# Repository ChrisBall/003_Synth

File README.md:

# 003_Synth
Code &amp; files for making my audio-lib based synth; 003

Based on a teensy 4.0 with assoc. audio board.

The synth is actually 2 devices - a teensy 4.0 with audio board and a separate "nano every"-based midi controller, with 48 pots, a rotary encoder and OLED display. 

Description of the contents of the code folder:

-"003_synth_main" contains the main arduino sketch.

-"Processing_003_controller_board" contains a basic processing sketch for controlling the synth using [the midibus](https://github.com/sparks/themidibus) library.

-"ctrlr interface" contains a similar midi interface for the [ctrlr software](https://github.com/RomanKubiak/ctrlr).

-"modified audio lib files" contains a modified delay effect for tape simulation. You'll need to replace the originals in the teensy audio lib folder.

-"nano_controller" contains the code that runs on the HMI controller.

You can use this code without building a controller - the synth can be controlled via MIDI. There is a processing program or ctrlr interface in the code folder to facilitate this.

Compilation notes:

-To compile my digital "tape" delay module you'll need to replace the teensy audio lib files (effect_delay.cpp and effect_delay.h) with my versions in the "modified audio lib files" folder.
-Build with "smallest code" option

To get it making a sound, there's some extra work:

-You'll need to set the master volume (CC44, channel 3 - the device only responds to controller values on channel 3). 
-To get sound through the effects chain, set the two distortion gains (CC25, CC41 - channel 3) which default to 0.
-To save a preset (SD card required) send program change on channel 16. To load: program change on channel 3. Presets are saved as plain text in folder "/PRESETS/" on the SD.

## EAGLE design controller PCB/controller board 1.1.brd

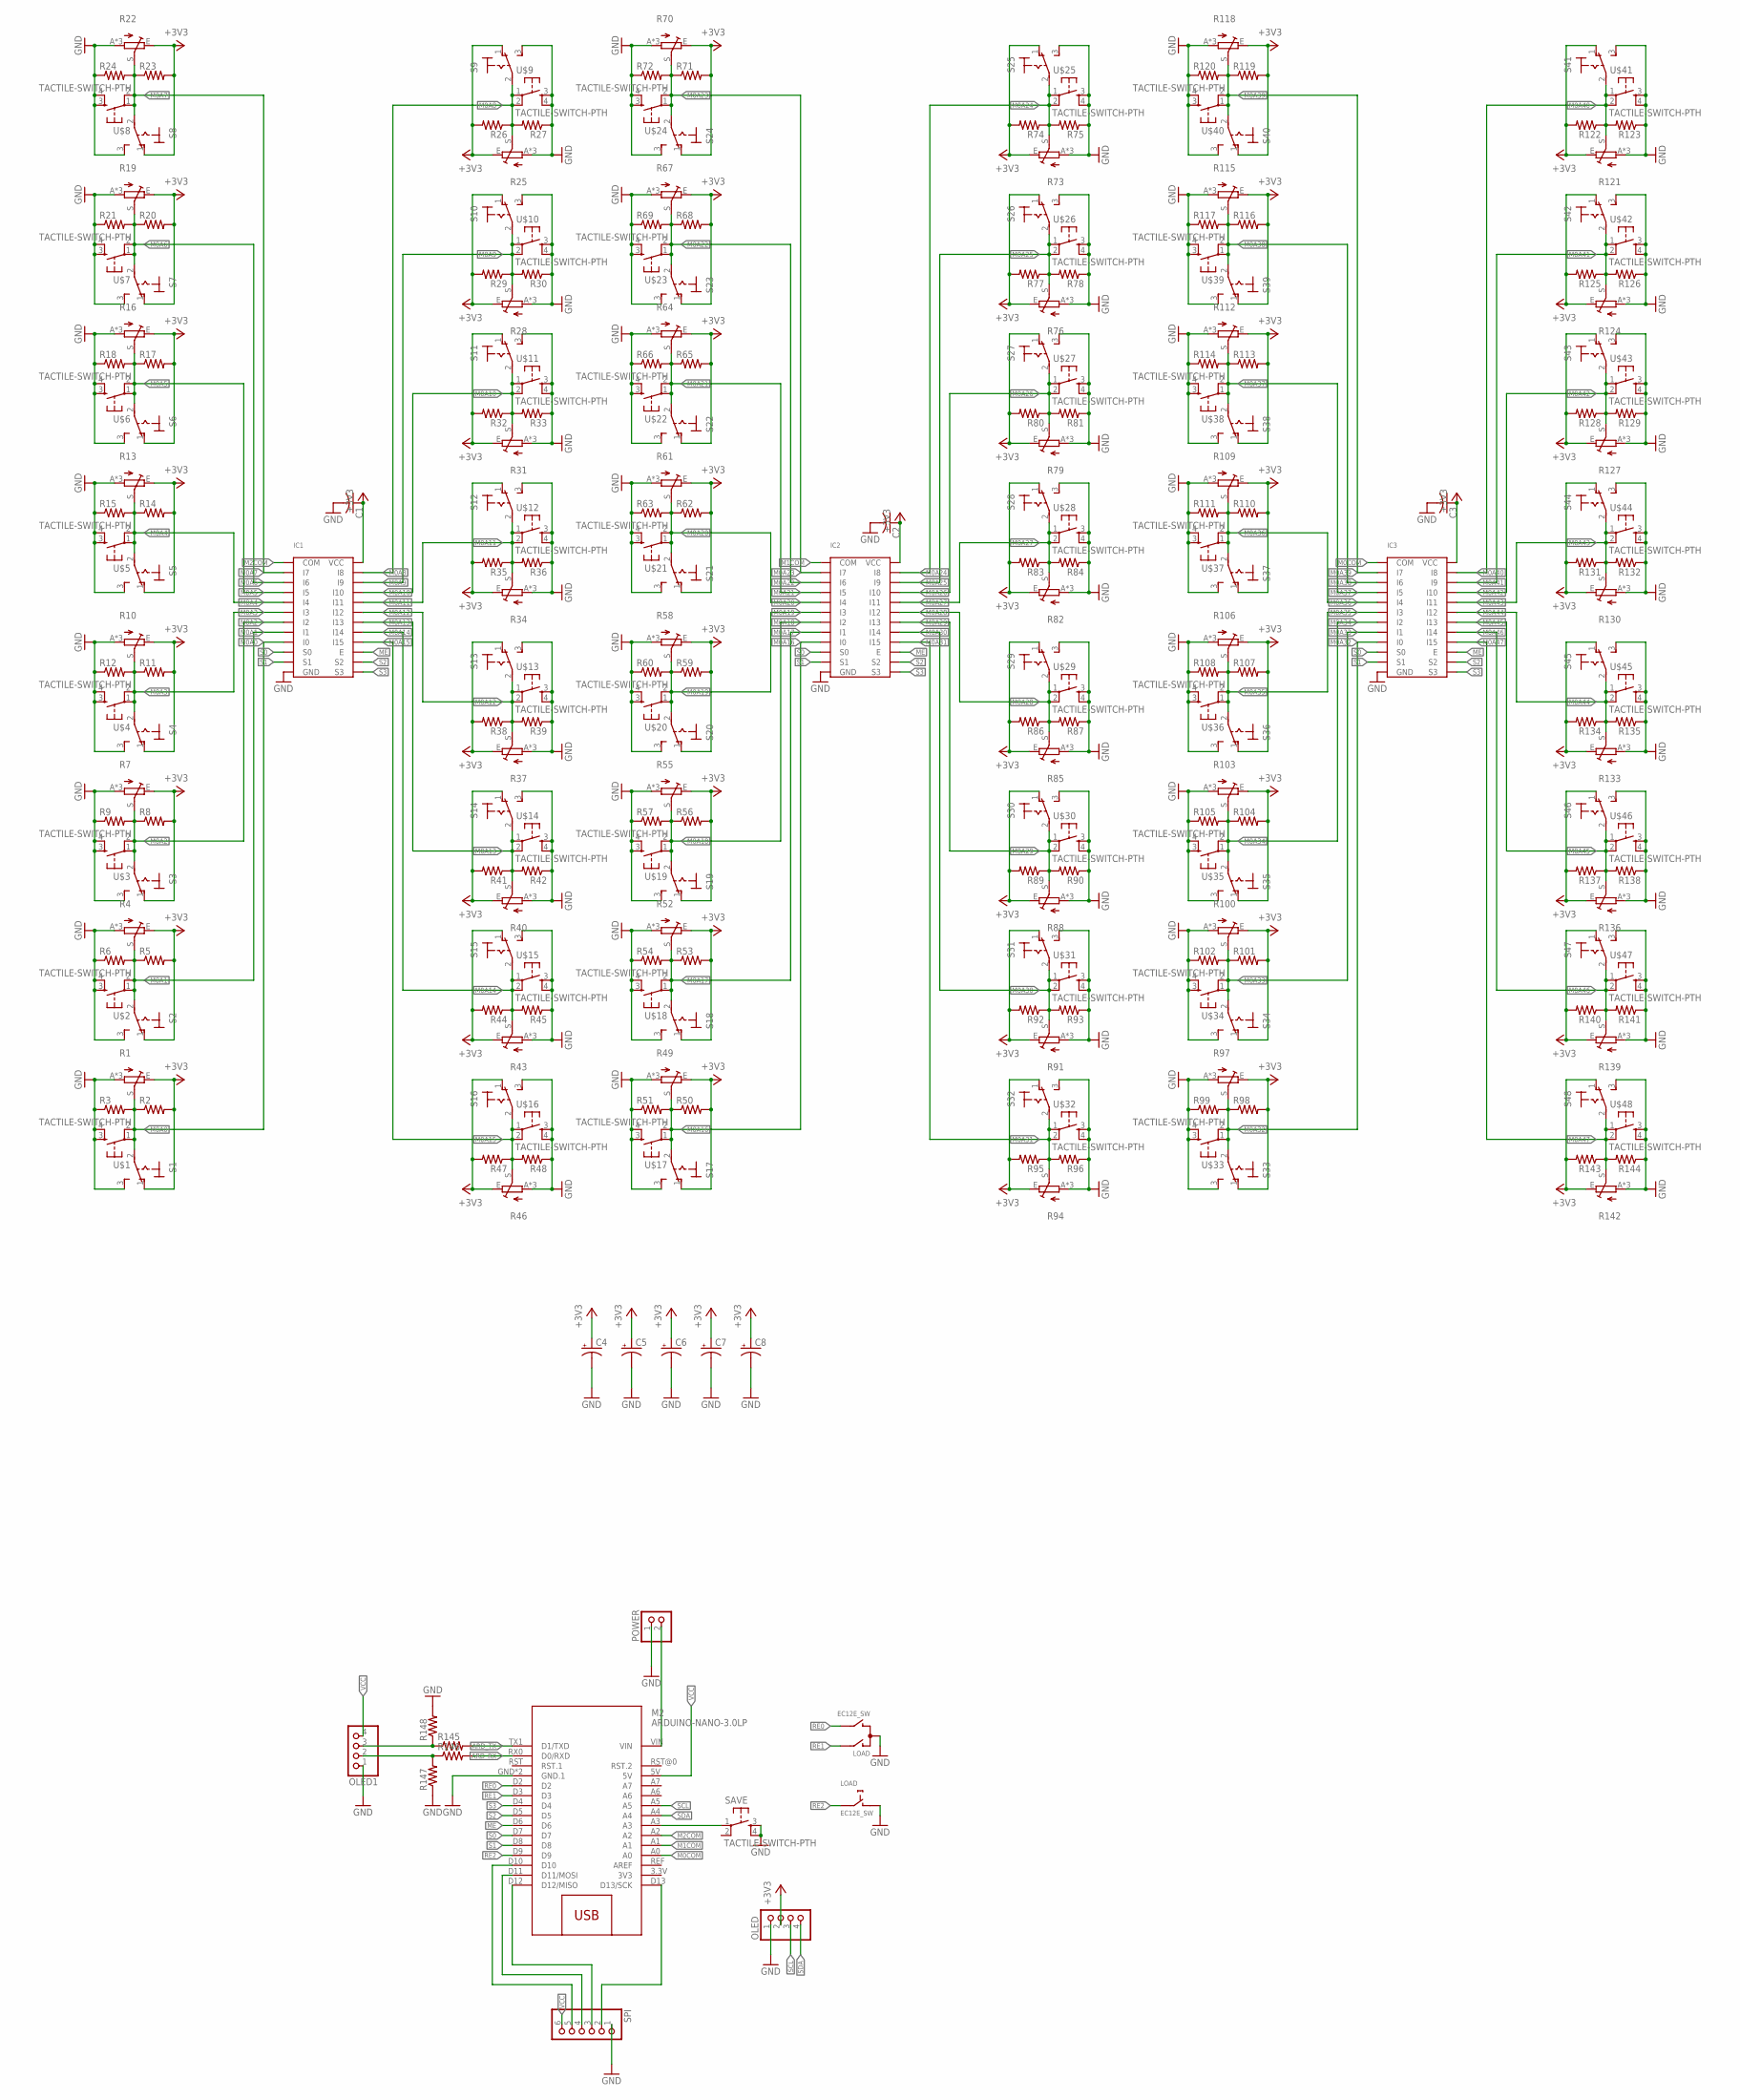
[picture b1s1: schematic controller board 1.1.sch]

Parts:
C1, C2, C3: C-USC0805; C0805
C4, C5, C6, C7, C8: CPOL-USE2.5-6; E2,5-6
IC1, IC2, IC3: CD74HC4067SM96; LP24SSOP
LOAD: EC12E_SW; ALPS_EC12E_SW
M2: ARDUINO-NANO-3.0LP; ARDUINO-NANO-3.0_LONGPADS
OLED, OLED1: PINHD-1X4; 1X04
POWER: PINHD-1X2; 1X02
R1, R4, R7, R10, R13, R16, R19, R22, R25, R28, R31, R34, R37, R40, R43, R46, R49, R52, R55, R58, R61, R64, R67, R70, R73, R76, R79, R82, R85, R88, R91, R94, R97, R100, R103, R106, R109, R112, R115, R118, R121, R124, R127, R130, R133, R136, R139, R142: TDS3_TRIM_EU-RK09LS; TDS3_RK09L
R2, R3, R5, R6, R8, R9, R11, R12, R14, R15, R17, R18, R20, R21, R23, R24, R26, R27, R29, R30, R32, R33, R35, R36, R38, R39, R41, R42, R44, R45, R47, R48, R50, R51, R53, R54, R56, R57, R59, R60, R62, R63, R65, R66, R68, R69, R71, R72, R74, R75, R77, R78, R80, R81, R83, R84, R86, R87, R89, R90, R92, R93, R95, R96, R98, R99, R101, R102, R104, R105, R107, R108, R110, R111, R113, R114, R116, R117, R119, R120, R122, R123, R125, R126, R128, R129, R131, R132, R134, R135, R137, R138, R140, R141, R143, R144, R145, R146, R147, R148: R-US_M0805; M0805
S1, S2, S3, S4, S5, S6, S7, S8, S9, S10, S11, S12, S13, S14, S15, S16, S17, S18, S19, S20, S21, S22, S23, S24, S25, S26, S27, S28, S29, S30, S31, S32, S33, S34, S35, S36, S37, S38, S39, S40, S41, S42, S43, S44, S45, S46, S47, S48: M9040P
SAVE: TACTILE-SWITCH-PTH; TAC-SWITCH-PTH
SPI: PINHD-1X6; 1X06
U$1, U$2, U$3, U$4, U$5, U$6, U$7, U$8, U$9, U$10, U$11, U$12, U$13, U$14, U$15, U$16, U$17, U$18, U$19, U$20, U$21, U$22, U$23, U$24, U$25, U$26, U$27, U$28, U$29, U$30, U$31, U$32, U$33, U$34, U$35, U$36, U$37, U$38, U$39, U$40, U$41, U$42, U$43, U$44, U$45, U$46, U$47, U$48: TACTILE-SWITCH-PTH; TAC-SWITCH-PTH

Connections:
3V3: M2.3.3V (3V3)
ARD_RX: M2.RX0 (D0/RXD), R146.2
ARD_TX: M2.TX1 (D1/TXD), R145.2
GND: C1.2, C2.2, C3.2, C4.-, C5.-, C6.-, C7.-, C8.-, IC1.GND, IC2.GND, IC3.GND, LOAD.C, LOAD.D (1), M2.GND (GND.1), M2.GND@1 (GND.1), OLED.1, OLED1.1, POWER.1, R1.A, R1.SNAPL (A), R1.SNAPR (A), R3.1, R4.A, R4.SNAPL (A), R4.SNAPR (A), R6.1, R7.A, R7.SNAPL (A), R7.SNAPR (A), R9.1, R10.A, R10.SNAPL (A), R10.SNAPR (A), R12.1, R13.A, R13.SNAPL (A), R13.SNAPR (A), R15.1, R16.A, R16.SNAPL (A), R16.SNAPR (A), R18.1, R19.A, R19.SNAPL (A), R19.SNAPR (A), R21.1, R22.A, R22.SNAPL (A), R22.SNAPR (A), R24.1, R25.A, R25.SNAPL (A), R25.SNAPR (A), R27.1, R28.A, R28.SNAPL (A), R28.SNAPR (A), R30.1, R31.A, R31.SNAPL (A), R31.SNAPR (A), R33.1, R34.A, R34.SNAPL (A), R34.SNAPR (A), R36.1, R37.A, R37.SNAPL (A), R37.SNAPR (A), R39.1, R40.A, R40.SNAPL (A), R40.SNAPR (A), R42.1, R43.A, R43.SNAPL (A), R43.SNAPR (A), R45.1, R46.A, R46.SNAPL (A), R46.SNAPR (A), R48.1, R49.A, R49.SNAPL (A), R49.SNAPR (A), R51.1, R52.A, R52.SNAPL (A), R52.SNAPR (A), R54.1, R55.A, R55.SNAPL (A), R55.SNAPR (A), R57.1, R58.A, R58.SNAPL (A), R58.SNAPR (A), R60.1, R61.A, R61.SNAPL (A), R61.SNAPR (A), R63.1, R64.A, R64.SNAPL (A), R64.SNAPR (A), R66.1, R67.A, R67.SNAPL (A), R67.SNAPR (A), R69.1, R70.A, R70.SNAPL (A), R70.SNAPR (A), R72.1, R73.A, R73.SNAPL (A), R73.SNAPR (A), R75.1, R76.A, R76.SNAPL (A), R76.SNAPR (A), R78.1, R79.A, R79.SNAPL (A), R79.SNAPR (A), R81.1, R82.A, R82.SNAPL (A), R82.SNAPR (A), R84.1, R85.A, R85.SNAPL (A), R85.SNAPR (A), R87.1, R88.A, R88.SNAPL (A), R88.SNAPR (A), R90.1, R91.A, R91.SNAPL (A), R91.SNAPR (A), R93.1, R94.A, R94.SNAPL (A), R94.SNAPR (A), R96.1, R97.A, R97.SNAPL (A), R97.SNAPR (A), R99.1, R100.A, R100.SNAPL (A), R100.SNAPR (A), R102.1, R103.A, R103.SNAPL (A), R103.SNAPR (A), R105.1, R106.A, R106.SNAPL (A), R106.SNAPR (A), R108.1, R109.A, R109.SNAPL (A), R109.SNAPR (A), R111.1, R112.A, R112.SNAPL (A), R112.SNAPR (A), R114.1, R115.A, R115.SNAPL (A), R115.SNAPR (A), R117.1, R118.A, R118.SNAPL (A), R118.SNAPR (A), R120.1, R121.A, R121.SNAPL (A), R121.SNAPR (A), R123.1, R124.A, R124.SNAPL (A), R124.SNAPR (A), R126.1, R127.A, R127.SNAPL (A), R127.SNAPR (A), R129.1, R130.A, R130.SNAPL (A), R130.SNAPR (A), R132.1, R133.A, R133.SNAPL (A), R133.SNAPR (A), R135.1, R136.A, R136.SNAPL (A), R136.SNAPR (A), R138.1, R139.A, R139.SNAPL (A), R139.SNAPR (A), R141.1, R142.A, R142.SNAPL (A), R142.SNAPR (A), R144.1, R147.1, R148.2, S1.3 (S), S2.3 (S), S3.3 (S), S4.3 (S), S5.3 (S), S6.3 (S), S7.3 (S), S8.3 (S), S9.3 (S), S10.3 (S), S11.3 (S), S12.3 (S), S13.3 (S), S14.3 (S), S15.3 (S), S16.3 (S), S17.3 (S), S18.3 (S), S19.3 (S), S20.3 (S), S21.3 (S), S22.3 (S), S23.3 (S), S24.3 (S), S25.3 (S), S26.3 (S), S27.3 (S), S28.3 (S), S29.3 (S), S30.3 (S), S31.3 (S), S32.3 (S), S33.3 (S), S34.3 (S), S35.3 (S), S36.3 (S), S37.3 (S), S38.3 (S), S39.3 (S), S40.3 (S), S41.3 (S), S42.3 (S), S43.3 (S), S44.3 (S), S45.3 (S), S46.3 (S), S47.3 (S), S48.3 (S), SAVE.3, SAVE.4, SPI.1, U$1.3, U$1.4, U$2.3, U$2.4, U$3.3, U$3.4, U$4.3, U$4.4, U$5.3, U$5.4, U$6.3, U$6.4, U$7.3, U$7.4, U$8.3, U$8.4, U$9.3, U$9.4, U$10.3, U$10.4, U$11.3, U$11.4, U$12.3, U$12.4, U$13.3, U$13.4, U$14.3, U$14.4, U$15.3, U$15.4, U$16.3, U$16.4, U$17.3, U$17.4, U$18.3, U$18.4, U$19.3, U$19.4, U$20.3, U$20.4, U$21.3, U$21.4, U$22.3, U$22.4, U$23.3, U$23.4, U$24.3, U$24.4, U$25.3, U$25.4, U$26.3, U$26.4, U$27.3, U$27.4, U$28.3, U$28.4, U$29.3, U$29.4, U$30.3, U$30.4, U$31.3, U$31.4, U$32.3, U$32.4, U$33.3, U$33.4, U$34.3, U$34.4, U$35.3, U$35.4, U$36.3, U$36.4, U$37.3, U$37.4, U$38.3, U$38.4, U$39.3, U$39.4, U$40.3, U$40.4, U$41.3, U$41.4, U$42.3, U$42.4, U$43.3, U$43.4, U$44.3, U$44.4, U$45.3, U$45.4, U$46.3, U$46.4, U$47.3, U$47.4, U$48.3, U$48.4
M0A0: IC1.I0, R1.S, R2.1, R3.2, S1.2, U$1.1, U$1.2
M0A1: IC1.I1, R4.S, R5.1, R6.2, S2.2, U$2.1, U$2.2
M0A2: IC1.I2, R7.S, R8.1, R9.2, S3.2, U$3.1, U$3.2
M0A3: IC1.I3, R10.S, R11.1, R12.2, S4.2, U$4.1, U$4.2
M0A4: IC1.I4, R13.S, R14.1, R15.2, S5.2, U$5.1, U$5.2
M0A5: IC1.I5, R16.S, R17.1, R18.2, S6.2, U$6.1, U$6.2
M0A6: IC1.I6, R19.S, R20.1, R21.2, S7.2, U$7.1, U$7.2
M0A7: IC1.I7, R22.S, R23.1, R24.2, S8.2, U$8.1, U$8.2
M0A8: IC1.I8, R25.S, R26.1, R27.2, S9.2, U$9.1, U$9.2
M0A9: IC1.I9, R28.S, R29.1, R30.2, S10.2, U$10.1, U$10.2
M0A10: IC1.I10, R31.S, R32.1, R33.2, S11.2, U$11.1, U$11.2
M0A11: IC1.I11, R34.S, R35.1, R36.2, S12.2, U$12.1, U$12.2
M0A12: IC1.I12, R37.S, R38.1, R39.2, S13.2, U$13.1, U$13.2
M0A13: IC1.I13, R40.S, R41.1, R42.2, S14.2, U$14.1, U$14.2
M0A14: IC1.I14, R43.S, R44.1, R45.2, S15.2, U$15.1, U$15.2
M0A15: IC1.I15, R46.S, R47.1, R48.2, S16.2, U$16.1, U$16.2
M0A16: IC2.I0, R49.S, R50.1, R51.2, S17.2, U$17.1, U$17.2
M0A17: IC2.I1, R52.S, R53.1, R54.2, S18.2, U$18.1, U$18.2
M0A18: IC2.I2, R55.S, R56.1, R57.2, S19.2, U$19.1, U$19.2
M0A19: IC2.I3, R58.S, R59.1, R60.2, S20.2, U$20.1, U$20.2
M0A20: IC2.I4, R61.S, R62.1, R63.2, S21.2, U$21.1, U$21.2
M0A21: IC2.I5, R64.S, R65.1, R66.2, S22.2, U$22.1, U$22.2
M0A22: IC2.I6, R67.S, R68.1, R69.2, S23.2, U$23.1, U$23.2
M0A23: IC2.I7, R70.S, R71.1, R72.2, S24.2, U$24.1, U$24.2
M0A24: IC2.I8, R73.S, R74.1, R75.2, S25.2, U$25.1, U$25.2
M0A25: IC2.I9, R76.S, R77.1, R78.2, S26.2, U$26.1, U$26.2
M0A26: IC2.I10, R79.S, R80.1, R81.2, S27.2, U$27.1, U$27.2
M0A27: IC2.I11, R82.S, R83.1, R84.2, S28.2, U$28.1, U$28.2
M0A28: IC2.I12, R85.S, R86.1, R87.2, S29.2, U$29.1, U$29.2
M0A29: IC2.I13, R88.S, R89.1, R90.2, S30.2, U$30.1, U$30.2
M0A30: IC2.I14, R91.S, R92.1, R93.2, S31.2, U$31.1, U$31.2
M0A31: IC2.I15, R94.S, R95.1, R96.2, S32.2, U$32.1, U$32.2
M0A32: IC3.I0, R97.S, R98.1, R99.2, S33.2, U$33.1, U$33.2
M0A33: IC3.I1, R100.S, R101.1, R102.2, S34.2, U$34.1, U$34.2
M0A34: IC3.I2, R103.S, R104.1, R105.2, S35.2, U$35.1, U$35.2
M0A35: IC3.I3, R106.S, R107.1, R108.2, S36.2, U$36.1, U$36.2
M0A36: IC3.I4, R109.S, R110.1, R111.2, S37.2, U$37.1, U$37.2
M0A37: IC3.I5, R112.S, R113.1, R114.2, S38.2, U$38.1, U$38.2
M0A38: IC3.I6, R115.S, R116.1, R117.2, S39.2, U$39.1, U$39.2
M0A39: IC3.I7, R118.S, R119.1, R120.2, S40.2, U$40.1, U$40.2
M0A40: IC3.I8, R121.S, R122.1, R123.2, S41.2, U$41.1, U$41.2
M0A41: IC3.I9, R124.S, R125.1, R126.2, S42.2, U$42.1, U$42.2
M0A42: IC3.I10, R127.S, R128.1, R129.2, S43.2, U$43.1, U$43.2
M0A43: IC3.I11, R130.S, R131.1, R132.2, S44.2, U$44.1, U$44.2
M0A44: IC3.I12, R133.S, R134.1, R135.2, S45.2, U$45.1, U$45.2
M0A45: IC3.I13, R136.S, R137.1, R138.2, S46.2, U$46.1, U$46.2
M0A46: IC3.I14, R139.S, R140.1, R141.2, S47.2, U$47.1, U$47.2
M0A47: IC3.I15, R142.S, R143.1, R144.2, S48.2, U$48.1, U$48.2
M0COM: IC3.COM, M2.A0
M1COM: IC2.COM, M2.A1
M2COM: IC1.COM, M2.A2
ME: IC1.E, IC2.E, IC3.E, M2.D6
unnamed: M2.D10, SPI.5
unnamed: M2.D11 (D11/MOSI), SPI.4
unnamed: M2.D12 (D12/MISO), SPI.3
unnamed: M2.VIN, POWER.2
unnamed: M2.A3, SAVE.1
unnamed: M2.D13 (D13/SCK), SPI.2
unnamed: OLED1.3, R145.1, R148.1
unnamed: OLED1.2, R146.1, R147.2
RE0: LOAD.B, M2.D2
RE1: LOAD.A, M2.D3
RE2: LOAD.E (2), M2.D9
S0: IC1.S0, IC2.S0, IC3.S0, M2.D7
S1: IC1.S1, IC2.S1, IC3.S1, M2.D8
S2: IC1.S2, IC2.S2, IC3.S2, M2.D5
S3: IC1.S3, IC2.S3, IC3.S3, M2.D4
SCL: M2.A5, OLED.3
SDA: M2.A4, OLED.4
VCC: C1.1, C2.1, C3.1, C4.+, C5.+, C6.+, C7.+, C8.+, IC1.VCC, IC2.VCC, IC3.VCC, M2.5V, OLED.2, OLED1.4, R1.E, R2.2, R4.E, R5.2, R7.E, R8.2, R10.E, R11.2, R13.E, R14.2, R16.E, R17.2, R19.E, R20.2, R22.E, R23.2, R25.E, R26.2, R28.E, R29.2, R31.E, R32.2, R34.E, R35.2, R37.E, R38.2, R40.E, R41.2, R43.E, R44.2, R46.E, R47.2, R49.E, R50.2, R52.E, R53.2, R55.E, R56.2, R58.E, R59.2, R61.E, R62.2, R64.E, R65.2, R67.E, R68.2, R70.E, R71.2, R73.E, R74.2, R76.E, R77.2, R79.E, R80.2, R82.E, R83.2, R85.E, R86.2, R88.E, R89.2, R91.E, R92.2, R94.E, R95.2, R97.E, R98.2, R100.E, R101.2, R103.E, R104.2, R106.E, R107.2, R109.E, R110.2, R112.E, R113.2, R115.E, R116.2, R118.E, R119.2, R121.E, R122.2, R124.E, R125.2, R127.E, R128.2, R130.E, R131.2, R133.E, R134.2, R136.E, R137.2, R139.E, R140.2, R142.E, R143.2, S1.1 (O), S2.1 (O), S3.1 (O), S4.1 (O), S5.1 (O), S6.1 (O), S7.1 (O), S8.1 (O), S9.1 (O), S10.1 (O), S11.1 (O), S12.1 (O), S13.1 (O), S14.1 (O), S15.1 (O), S16.1 (O), S17.1 (O), S18.1 (O), S19.1 (O), S20.1 (O), S21.1 (O), S22.1 (O), S23.1 (O), S24.1 (O), S25.1 (O), S26.1 (O), S27.1 (O), S28.1 (O), S29.1 (O), S30.1 (O), S31.1 (O), S32.1 (O), S33.1 (O), S34.1 (O), S35.1 (O), S36.1 (O), S37.1 (O), S38.1 (O), S39.1 (O), S40.1 (O), S41.1 (O), S42.1 (O), S43.1 (O), S44.1 (O), S45.1 (O), S46.1 (O), S47.1 (O), S48.1 (O), SPI.6

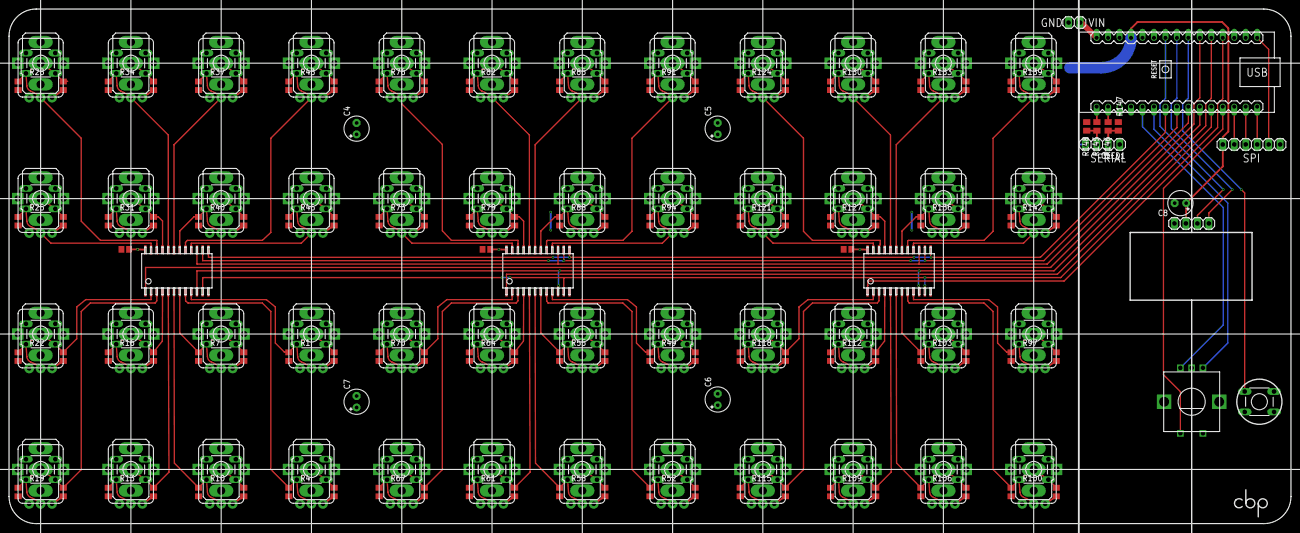
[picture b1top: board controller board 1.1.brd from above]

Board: 2 copper layers, 284.0 x 114.0 mm, 262 parts (0 on the bottom side), 73 nets.

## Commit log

2021-08-20 Deleted unneccesary file
2022-03-14 More useful instructions
2022-06-28 Added ctrlr interface
    adding crtlr interface provided by https://github.com/HLammers
2022-06-28 Updated readme to reflect ctrlr

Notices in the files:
parts and their libraries:
GeekAmmo: Licensing:Creative Commons ShareAlike 4.0 International - https://creativecommons.org/licenses/by-sa/4.0
diy-modules: Released under the Creative Commons Attribution 4.0 International License: http://creativecommons.org/licenses/by/4.0
